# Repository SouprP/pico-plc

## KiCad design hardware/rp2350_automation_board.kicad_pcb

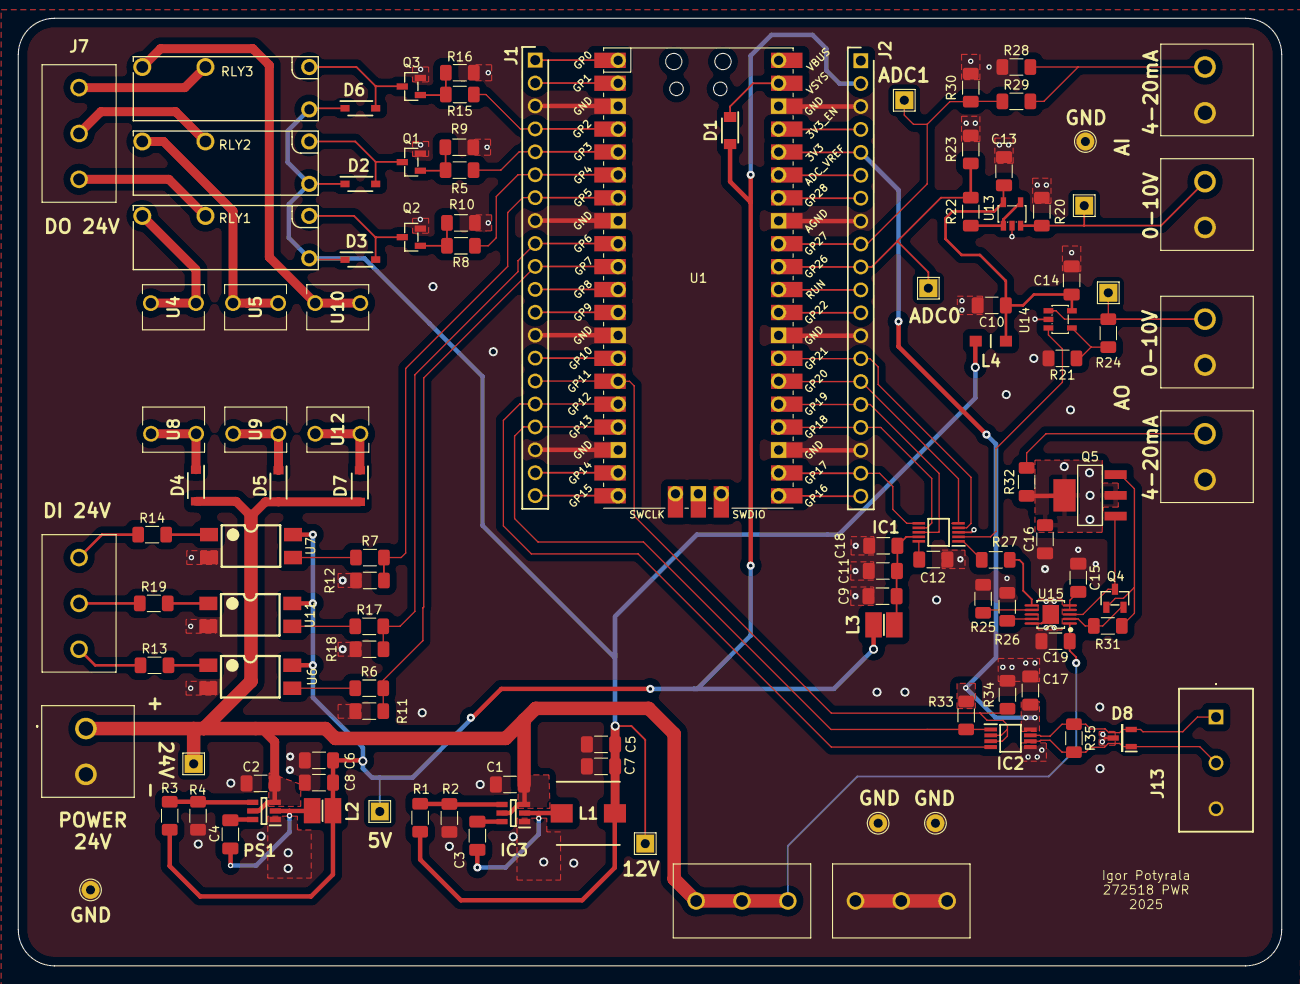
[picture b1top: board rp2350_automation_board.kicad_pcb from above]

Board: 2 copper layers, 140.0 x 105.0 mm, 114 parts (0 on the bottom side), 86 nets.

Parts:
C1, C2: 2.2uF; C_1206_3216Metric_Pad1.33x1.80mm_HandSolder
C3, C4, C13, C14, C17, C19: 0.1uF; C_1206_3216Metric_Pad1.33x1.80mm_HandSolder
C5, C7: 22uF; C_1206_3216Metric_Pad1.33x1.80mm_HandSolder
C6, C8, C9, C10: 10uF; C_1206_3216Metric_Pad1.33x1.80mm_HandSolder
C11: 1uF; C_1206_3216Metric_Pad1.33x1.80mm_HandSolder
C12: 150nF; C_1206_3216Metric_Pad1.33x1.80mm_HandSolder
C15: 470nF; C_1206_3216Metric_Pad1.33x1.80mm_HandSolder
C16: 10nF; C_1206_3216Metric_Pad1.33x1.80mm_HandSolder
C18: 1nF; C_1206_3216Metric_Pad1.33x1.80mm_HandSolder
D1: MBR230S1F-7; SODFL3518X115N
D2, D3, D6: 1N4148W; SODFL3816X120N
D4, D5, D7: 1N4007W-T; SODFL3818X130N
D8: CDSOT23-SM712; SOT95P230X117-3N
IC1: DAC7562SDGSR; SOP50P490X110-10N
IC2: SN65HVD75DGKR; SOP65P490X110-8N
IC3: LMR51420XFDDCR; SOT95P280X110-6N
J1, J2: PH1-20-UA; HDRV20W64P0X254_1X20_5080X249X886P
J3, J4, J7, J14: TB006-508-03BE; TB00650803BE
J5, J9, J10, J11, J12: TB007-508-02BE; TB00750802BE
J13: 39880-0303; 398800303
L1: 22uH; INDPM7070X480N
L2, L3: 4.7uH; INDC3225X120N
L4: 1uH; LQM31PN1R0M00L
PS1: LMR51420YFDDCR; SOT95P280X110-6N
Q1, Q2, Q3: 2N7002; SOT-23-3_L2.9-W1.3-P1.90-LS2.4-BR
Q4: MMBT2907ALT1G; SOT-23-3_L2.9-W1.3-P1.90-LS2.4-BR
Q5: BSP171PH6327XTSA1; SOT-223-4_L6.5-W3.5-P2.30-LS7.0-BR
R1, R3, R20: 100k; R_1206_3216Metric_Pad1.30x1.75mm_HandSolder
R2: 5.23k; R_1206_3216Metric_Pad1.30x1.75mm_HandSolder
R4: 13.7k; R_1206_3216Metric_Pad1.30x1.75mm_HandSolder
R5, R8, R15: 330; R_1206_3216Metric_Pad1.30x1.75mm_HandSolder
R6, R7, R9, R10, R16, R17, R21, R26, R33, R34: 10k; R_1206_3216Metric_Pad1.30x1.75mm_HandSolder
R11, R12, R18: 20k; R_1206_3216Metric_Pad1.30x1.75mm_HandSolder
R13, R14, R19: 3.3k; R_1206_3216Metric_Pad1.30x1.75mm_HandSolder
R22: 56k; R_1206_3216Metric_Pad1.30x1.75mm_HandSolder
R23: 24k; R_1206_3216Metric_Pad1.30x1.75mm_HandSolder
R24: 30k; R_1206_3216Metric_Pad1.30x1.75mm_HandSolder
R25: 1.25k; R_1206_3216Metric_Pad1.30x1.75mm_HandSolder
R27: 0R; R_1206_3216Metric_Pad1.30x1.75mm_HandSolder
R28: 250R; R_1206_3216Metric_Pad1.30x1.75mm_HandSolder
R29: 22k; R_1206_3216Metric_Pad1.30x1.75mm_HandSolder
R30: 33k; R_1206_3216Metric_Pad1.30x1.75mm_HandSolder
R31, R32: 15; R_1206_3216Metric_Pad1.30x1.75mm_HandSolder
R35: 120R; R_1206_3216Metric_Pad1.30x1.75mm_HandSolder
RLY1, RLY2, RLY3: G5NB-1A-E-DC12; RELAY-TH_G5NB-1A-E-DCXX
TP1: TP_+12V; TestPoint_THTPad_2.0x2.0mm_Drill1.0mm
TP2, TP4, TP6, TP7: GND_TP; TestPoint_THTPad_D2.0mm_Drill1.0mm
TP3: TP_+5V; TestPoint_THTPad_2.0x2.0mm_Drill1.0mm
TP5: TP_+24V; TestPoint_THTPad_2.0x2.0mm_Drill1.0mm
TP8: TP_AO_0-10V; TestPoint_THTPad_2.0x2.0mm_Drill1.0mm
TP9: TP_ADC0; TestPoint_THTPad_2.0x2.0mm_Drill1.0mm
TP10: TP_AI_0-10V; TestPoint_THTPad_2.0x2.0mm_Drill1.0mm
TP11: TP_ADC1; TestPoint_THTPad_2.0x2.0mm_Drill1.0mm
U1: Pico; RPi_Pico_SMD_TH
U4, U5, U8, U9, U10, U12: FUSE_C; 01110501Z
U6, U7, U11: LTV-814S-TA1; SMD-4_L4.6-W6.5-P2.54-LS10.2-BL
U13, U14: TLV9301IDBVR; SOT-23-5_L3.0-W1.7-P0.95-LS2.8-BR
U15: XTR111AIDGQR; MSOP-10_L3.0-W3.0-P0.50-LS5.0-BL-EP

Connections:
5V_SW: C4.2, L2.1, PS1.2 (SW)
12V_SW: C3.2, IC3.2 (SW), L1.1
+3V3: C17.1, IC2.8 (VCC), J2.5, R33.1, U1.36 (3V3)
+5V: C6.1, C8.1, D1.2 (A), J2.2, L2.2, L3.1, R3.1, TP3.1, U6.4, U7.4, U11.4
+12V: C5.1, C7.1, D2.1 (K), D3.1 (K), D6.1 (K), L1.2, L4.1, R1.1, RLY1.4, RLY2.4, RLY3.4, TP1.1
+12V_LPF_OP: C10.1, C13.1, C14.1, L4.2, U13.5 (V+), U14.5 (V+)
+24V: C1.2, C2.2, C19.2, D4.2 (A), D5.2 (A), D7.2 (A), IC3.3 (VIN), IC3.5 (EN), J3.1, J3.2, J3.3, J5.1, PS1.3 (VIN), PS1.5 (EN), TP5.1, U15.1 (VSP)
/Analog IO/AI_0-10V_IN: J9.1, R20.2, TP10.1, U13.3 (+IN)
/Analog IO/AI_4-20mA_IN: J11.1, R28.2, R29.2
/Analog IO/AO_0-10V: J10.1, R24.1, TP8.1, U14.1 (OUT)
/Analog IO/AO_4-20mA: J12.1, R32.2
/Analog IO/DAC_0-10V: IC1.2 (VOUT_B), U14.3 (+IN)
/Analog IO/DAC_4-20mA: IC1.1 (VOUT_A), R27.2
/Digital IO/DI_1: J14.1, R13.1
/Digital IO/DI_2: J14.2, R19.1
/Digital IO/DI_3: J14.3, R14.1
/Digital IO/DO_1: J7.1, RLY1.2
/Digital IO/DO_2: J7.2, RLY2.2
/Digital IO/DO_3: J7.3, RLY3.2
/RS-485/RS485+: D8.2, IC2.7 (B), J13.1, R35.1
/RS-485/RS485-: D8.1, IC2.6 (A), J13.2, R35.2
ADC0: J2.10, R22.1, R23.2, TP9.1, U1.31 (GPIO26_ADC0)
ADC1: J2.9, R29.1, R30.2, TP11.1, U1.32 (GPIO27_ADC1)
DAC_LDAC: IC1.4 (~LDAC), J2.14, U1.27 (GPIO21)
DAC_RESET: IC1.5 (~CLR), J2.15, U1.26 (GPIO20)
DIN_1: J1.7, R7.2, R12.2, U1.7 (GPIO5)
DIN_2: J1.9, R17.2, R18.2, U1.9 (GPIO6)
DIN_3: J1.10, R6.2, R11.2, U1.10 (GPIO7)
DOUT_1: J1.4, R15.1, U1.4 (GPIO2)
DOUT_2: J1.5, R5.1, U1.5 (GPIO3)
DOUT_3: J1.6, R8.1, U1.6 (GPIO4)
GND: C1.1, C2.1, C5.2, C6.2, C7.2, C8.2, C9.2, C10.2, C11.1, C12.2, C13.2, C14.2, C15.1, C16.1, C17.2, C18.1, C19.1, D8.3, IC1.3 (GND), IC2.5 (GND), IC3.1 (GND), J1.3, J1.8, J1.13, J1.18, J2.3, J2.8, J2.13, J2.18, J4.1, J4.2, J4.3, J5.2, J9.2, J10.2, J11.2, J12.2, J13.3, PS1.1 (GND), Q1.2 (S), Q2.2 (S), Q3.2 (S), R2.2, R4.2, R9.1, R10.1, R11.1, R12.1, R16.1, R18.1, R20.1, R21.2, R23.1, R25.2, R26.2, R28.1, R30.1, R34.2, TP2.1, TP4.1, TP6.1, TP7.1, U1.3 (GND), U1.8 (GND), U1.13 (GND), U1.18 (GND), U1.23 (GND), U1.28 (GND), U1.33 (AGND), U1.38 (GND), U6.2, U7.2, U11.2, U13.2 (V-), U14.2 (V-), U15.10 (GND), U15.11 (PAD)
unnamed: C16.2, Q5.2 (D), Q5.4 (D), R32.1
unnamed: D1.1 (K), U1.39 (VSYS)
unnamed: D2.2 (A), Q1.3 (D), RLY2.1
unnamed: D3.2 (A), Q2.3 (D), RLY1.1
unnamed: D4.1 (K), U8.1, U8.2
unnamed: D5.1 (K), U9.1, U9.2
unnamed: D6.2 (A), Q3.3 (D), RLY3.1
unnamed: D7.1 (K), U12.1, U12.2
unnamed: C9.1, C11.2, C18.2, IC1.9 (AVDD), L3.2
unnamed: C12.1, IC1.10 (VREFIN/VREFOUT)
unnamed: C3.1, IC3.6 (CB)
unnamed: IC3.4 (FB), R1.2, R2.1
unnamed: C4.1, PS1.6 (CB)
unnamed: PS1.4 (FB), R3.2, R4.1
unnamed: Q1.1 (G), R5.2, R9.2
unnamed: Q2.1 (G), R8.2, R10.2
unnamed: Q3.1 (G), R15.2, R16.2
unnamed: Q4.1 (B), Q5.3 (S), R31.1
unnamed: Q4.3 (C), Q5.1 (G), U15.3 (VG)
unnamed: Q4.2 (E), R31.2, U15.2 (IS)
unnamed: R6.1, U6.3
unnamed: R7.1, U7.3
unnamed: R13.2, U6.1
unnamed: R14.2, U7.1
unnamed: R17.1, U11.3
unnamed: R19.2, U11.1
unnamed: RLY1.3, U4.1, U4.2
unnamed: RLY2.3, U5.1, U5.2
unnamed: RLY3.3, U10.1, U10.2
unnamed: J2.4, U1.37 (3V3_EN)
unnamed: J2.6, U1.35 (ADC_VREF)
unnamed: J1.1, U1.1 (GPIO0)
unnamed: J1.2, U1.2 (GPIO1)
unnamed: J1.11, U1.11 (GPIO8)
unnamed: J1.12, U1.12 (GPIO9)
unnamed: J1.14, U1.14 (GPIO10)
unnamed: J1.19, U1.19 (GPIO14)
unnamed: J1.20, U1.20 (GPIO15)
unnamed: J2.12, U1.29 (GPIO22)
unnamed: J2.7, U1.34 (GPIO28_ADC2)
unnamed: J2.11, U1.30 (RUN)
unnamed: R22.2, U13.1 (OUT), U13.4 (-IN)
unnamed: R21.1, R24.2, U14.4 (-IN)
unnamed: R26.1, U15.9 (OD)
unnamed: C15.2, U15.4 (REGS), U15.5 (REGF)
unnamed: R25.1, U15.7 (SET)
unnamed: R27.1, U15.6 (VIN)
RS485_MODE: IC2.2 (~RE), IC2.3 (DE), J1.15, R34.1, U1.15 (GPIO11)
SPI0_CS: IC1.6 (~SYNC), J2.19, U1.22 (GPIO17)
SPI0_MISO: J2.20, U1.21 (GPIO16)
SPI0_MOSI: IC1.8 (DIN), J2.16, U1.25 (GPIO19)
SPI0_SCK: IC1.7 (SCLK), J2.17, U1.24 (GPIO18)
UART_RX: IC2.1 (R), J1.17, R33.2, U1.17 (GPIO13)
UART_TX: IC2.4 (D), J1.16, U1.16 (GPIO12)

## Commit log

2025-10-05 Setup
2025-10-05 Dockerfile missing libs
2025-10-10 Modbus frame
2025-10-12 CMake fixes
2025-11-07 Windoows
2025-11-14 Automated CMake
2025-11-22 Modbus halfway
2025-11-24 4-20mA start and PWM as DAC
2025-11-25 XTR117 Output
2025-11-27 Almost everything
2025-12-01 Board complete
2025-12-01 LDAC added
2025-12-01 Fixes
2025-12-01 Ordered
2025-12-06 Modbus, small schematic changes
2025-12-08 Modbus library done
2025-12-08 UART parity and better timing handling
2025-12-09 main
2025-12-10 DAC and analog utils
2026-02-28 Finalization
